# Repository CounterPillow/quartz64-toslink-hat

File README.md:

SPDIF to TOSLink Adapter Hat for Quartz64
=========================================

This is a small 3 component PCB that allows you to plug a TOSLink cable into
your PINE64 Quartz64 single-board computer.

You'll need the following components for assembly:

- 2x3 long 2.54mm spacing female pin row headers, e.g. SSQ-103-03-G-D
- a 0.1µF ceramic capacitor for decoupling
- Everlight PLT133/T10W TOSLink transmitter

The last component is supposedly "obsolete" according to DigiKey, but they have
a lot of stock and other distributors seem somewhat confused about the
obsolescence of various products by this manufacturer. I wouldn't worry about
it too much.

The design/documentation is licensed as CERN-OHL-P (see LICENSE.txt).

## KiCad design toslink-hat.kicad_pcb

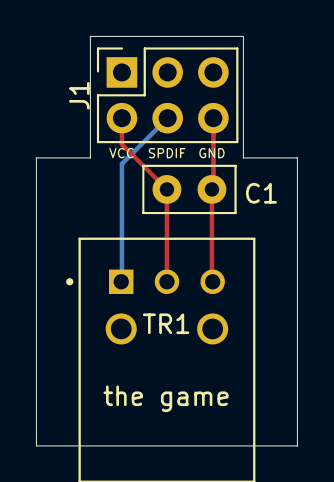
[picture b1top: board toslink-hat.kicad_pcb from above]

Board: 2 copper layers, 14.5 x 22.8 mm, 3 parts (0 on the bottom side), 3 nets.

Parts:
C1: 0.1uF; C_Disc_D5.0mm_W2.5mm_P2.50mm
J1: Conn_02x03; Socket_Strip_Straight_2x03_Pitch2.54mm
TR1: PLT133_T10W; T10W

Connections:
/GND: C1.2, J1.6, TR1.3
/SPDIF: J1.4, TR1.1
/VCC: C1.1, J1.2, TR1.2

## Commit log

2021-09-28 Add README

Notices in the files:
toslink-hat.kicad_pcb:
Licensed under CERN-OHL-P v2 or later
